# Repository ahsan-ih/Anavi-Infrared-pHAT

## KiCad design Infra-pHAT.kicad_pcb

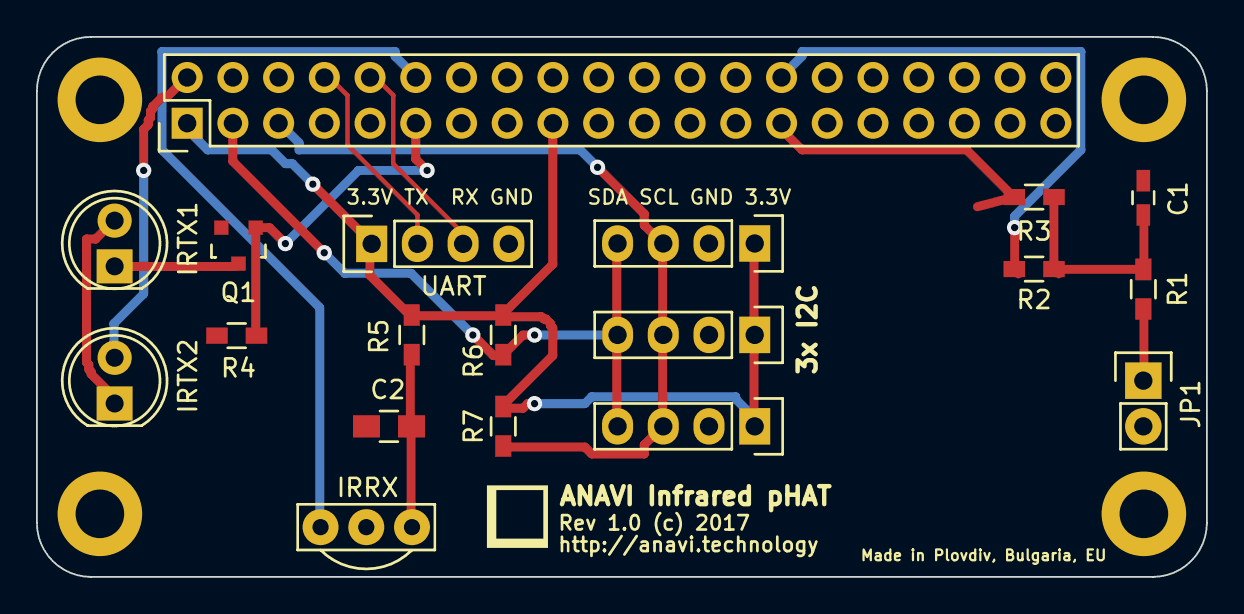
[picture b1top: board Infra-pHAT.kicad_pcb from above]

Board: 2 copper layers, 65.0 x 30.0 mm, 23 parts (0 on the bottom side), 15 nets.

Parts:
C1: 0.1; C_0603_HandSoldering
C2: 4.7; C_0805_HandSoldering
IRRX: TSOP34838; TSOP38X
IRTX1, IRTX2: L-53F3BT; LED-5MM
JP1: JUMPER; Pin_Header_Straight_1x02
Q1: BC817; SOT-23
R1: 1K; R_0603_HandSoldering
R2, R3, R6, R7: 4.7K; R_0603_HandSoldering
R4: 10K; R_0603_HandSoldering
R5: 470; R_0603_HandSoldering
RASP_CONN1: Raspberry_PI; Pin_Header_Straight_2x20
REF1, REF2, REF3, REF4: MountingHole_2.7mm_M2.5_DIN965_Pad
SENS1, SENS2, SENS3: I2C_SENS_1; Pin_Header_Straight_1x04
UART: CONN_01X04; Pin_Header_Straight_1x04

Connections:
+3V3: C1.1, R1.1, R2.1, R3.1, R5.1, R6.1, R7.1, RASP_CONN1.1, RASP_CONN1.17, SENS1.1, SENS2.1, SENS3.1, UART.1
+5V: IRTX2.2, RASP_CONN1.2, RASP_CONN1.4
/RXD: RASP_CONN1.10, UART.3
/TXD: RASP_CONN1.8, UART.2
GND: C1.2, C2.2, IRRX.2, JP1.2, Q1.2, R4.1, RASP_CONN1.6, RASP_CONN1.9, RASP_CONN1.14, RASP_CONN1.20, RASP_CONN1.25, RASP_CONN1.30, RASP_CONN1.34, RASP_CONN1.39, SENS1.2, SENS2.2, SENS3.2, UART.4
unnamed: C2.1, IRRX.3, R5.2
unnamed: IRRX.1, RASP_CONN1.12
unnamed: IRTX1.1, Q1.3
unnamed: IRTX1.2, IRTX2.1
unnamed: JP1.1, R1.2
unnamed: Q1.1, R4.2, RASP_CONN1.11
unnamed: R2.2, RASP_CONN1.28
unnamed: R3.2, RASP_CONN1.27
unnamed: R6.2, RASP_CONN1.3, SENS1.4, SENS2.4, SENS3.4
unnamed: R7.2, RASP_CONN1.5, SENS1.3, SENS2.3, SENS3.3

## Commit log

2020-01-09 initiated the project
2020-01-09 populated the schematic
2020-01-09 Schematic Complete.
2020-01-09 made the pcb template based on the Pi zero footprint
2020-01-09 Placed Connectors for: UART + IRTX
2020-01-09 Updated the I2C Connectors + Added Few Components
2020-01-09 Added DIP8 Footprint for CAT24C32WI-GT3
2020-01-09 front copper layer routed
2020-01-09 back copper layer routed
2020-01-09 deleted the front & back zones
2020-01-09 deleted the DIP8 footprint for CAT24C32WI-GT3
2020-01-09 placed the footprint for CAT24C32WI-GT3 & deleted the UART connector

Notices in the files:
Infra-pHAT.kicad_pcb:
Rev 1.0 (c) 2017
